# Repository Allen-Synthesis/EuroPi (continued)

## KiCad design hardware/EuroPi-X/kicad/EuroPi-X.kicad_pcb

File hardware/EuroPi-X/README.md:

# EuroPi X

The EuroPi X is an improved hardware version of the EuroPi. Its exact feature set is yet to be decided, but likely additions are more inputs, more outputs, better noise performance for inputs, better accuracy for outputs, a larger display, and larger flash storage.

Suggested features:
- RGB LEDs for outputs
  - [Neopixels](https://www.adafruit.com/product/4492?gclid=Cj0KCQjw2cWgBhDYARIsALggUhp21QpzSRPmMwkA5GLrfMsx_jSPfgyTrgrEi0MlV2bsC2WGbknoDSoaAqggEALw_wcB)?
  - Colour matches output type e.g. red for gate, blue for CV, green for 1v/oct
  - Colour determined automatically in code when a method is used, e.g. cv1.on() would automatically set it to red as a gate type
- DAC outputs (>=12 bit)
  - [MCP4728](https://shop.pimoroni.com/products/adafruit-mcp4728-quad-dac-with-eeprom-stemma-qt-qwiic?variant=31458498412627&currency=GBP&utm_source=google&utm_medium=cpc&utm_campaign=google+shopping?utm_source=google&utm_medium=surfaces&utm_campaign=shopping&gclid=Cj0KCQjwtsCgBhDEARIsAE7RYh3qANxNiQCtKDUFhGal1OTP4WOT_NSxUyUTKL1Pj_3x2VDyPnRayScaAk5DEALw_wcB)? 12 bit, 4 channel
  - Bipolar https://tinyurl.com/2abku7y3, jumper on the back of the module to set the mode, GPIO detects mode to allow code adjustments:

- More inputs
  - 4 inputs can fit in 8HP
- Higher performance CV inputs
  - External ADC, maybe with higher resolution
  - Separate analogue and digital power supplies using RP2040 AGND
- Ability to use +5V rail instead of internally generated
  - 16 pin header
  - Automatically use +5V rail if present, default to internally generated if not
- Make unused GPIO and USB signals accessible from the back
  - Keep one I2C/SPI bus unused so users don't have to worry about address clashes
  - Make sure USB signals are length matched
- Larger display (128x64 or larger)
  - [SSD1306](https://www.buydisplay.com/serial-spi-1-3-inch-128x64-oled-display-module-ssd1306-white-on-black) without breakout board (use Izaak's in progress board?) 
- Bipolar inputs
- Bipolar outputs
- Programmable I/O to allow unipolar or bipolar usage
  - Analogue switch IC? [DG4051 octa analog switch](https://www.mouser.co.uk/ProductDetail/Vishay-Siliconix/DG4051EEQ-T1-GE3?qs=367PjNmvCmmPtnHZ5hoXyA%3D%3D)
- Front access USB
- Front access reset and bootsel
- MicroSD slot for increased storage
- Increased flash by default
- Automatic detection of variant i.e. X or normal hardware
  - One GPIO tied to 3.3V, module detects it's an X if GPIO is high
  - Also set in config settings if module can't detect automatically

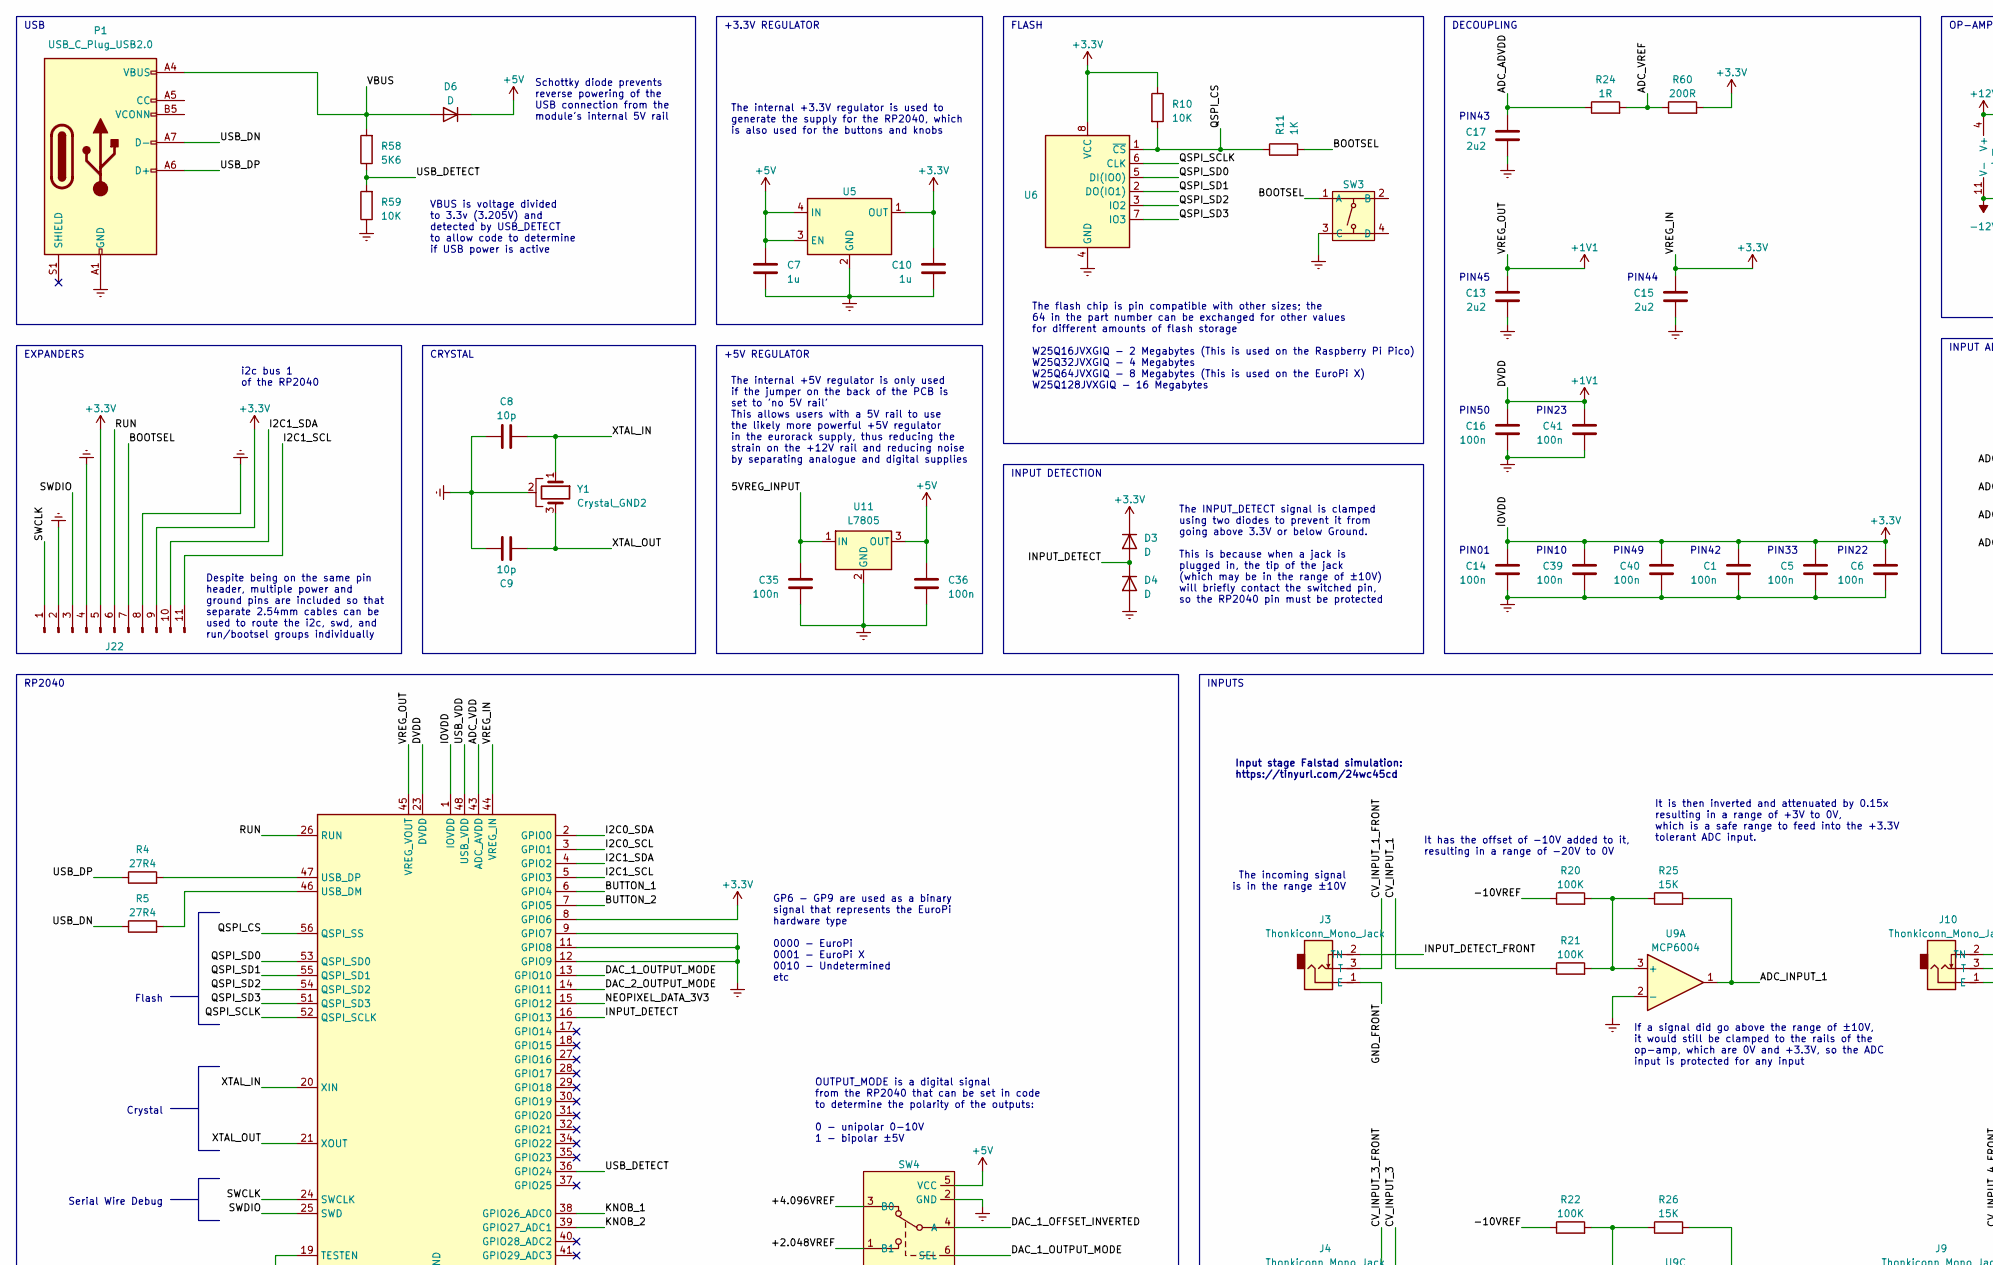
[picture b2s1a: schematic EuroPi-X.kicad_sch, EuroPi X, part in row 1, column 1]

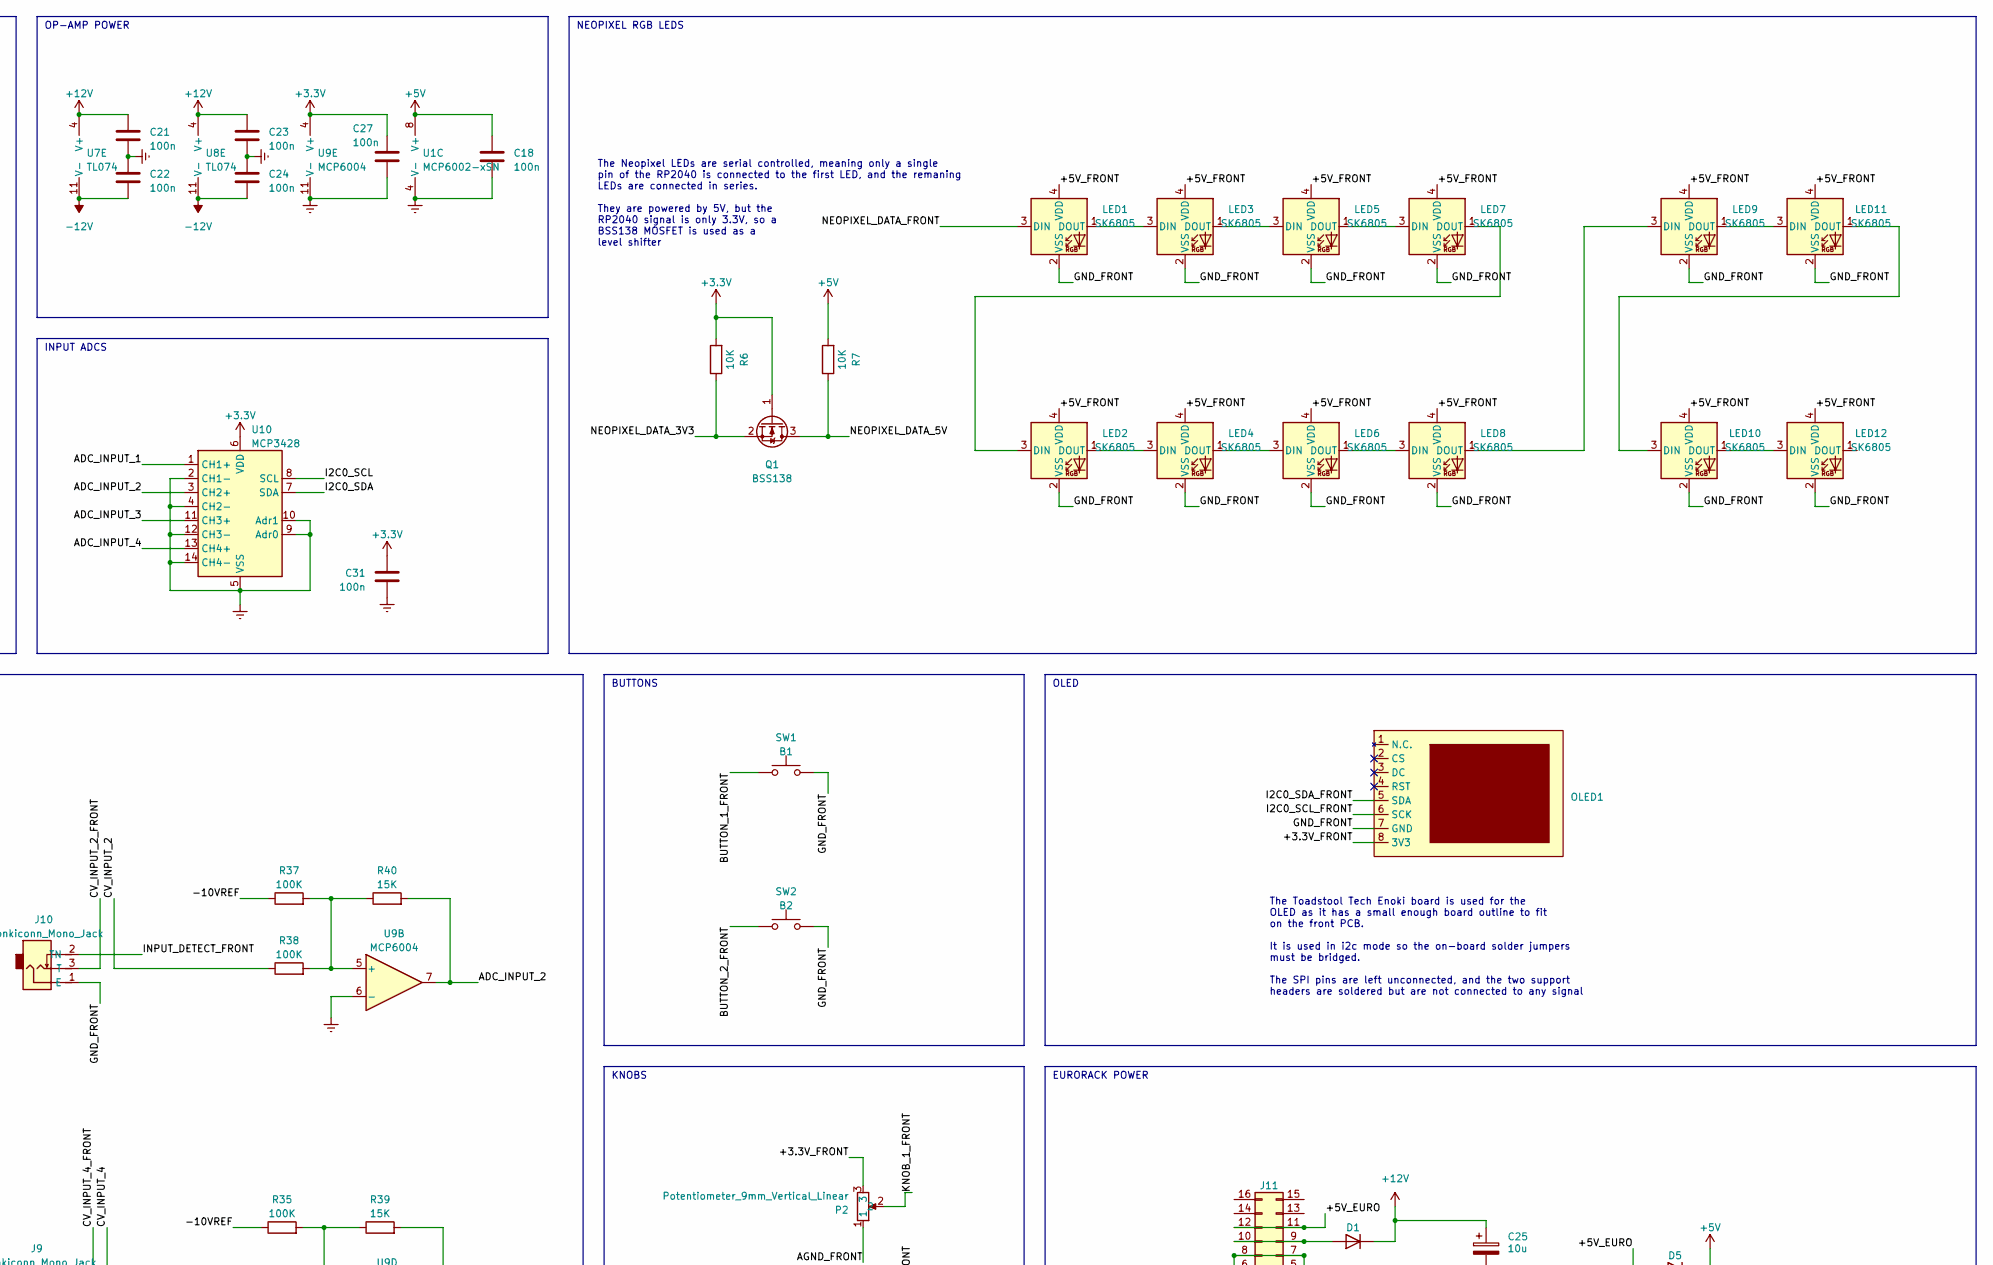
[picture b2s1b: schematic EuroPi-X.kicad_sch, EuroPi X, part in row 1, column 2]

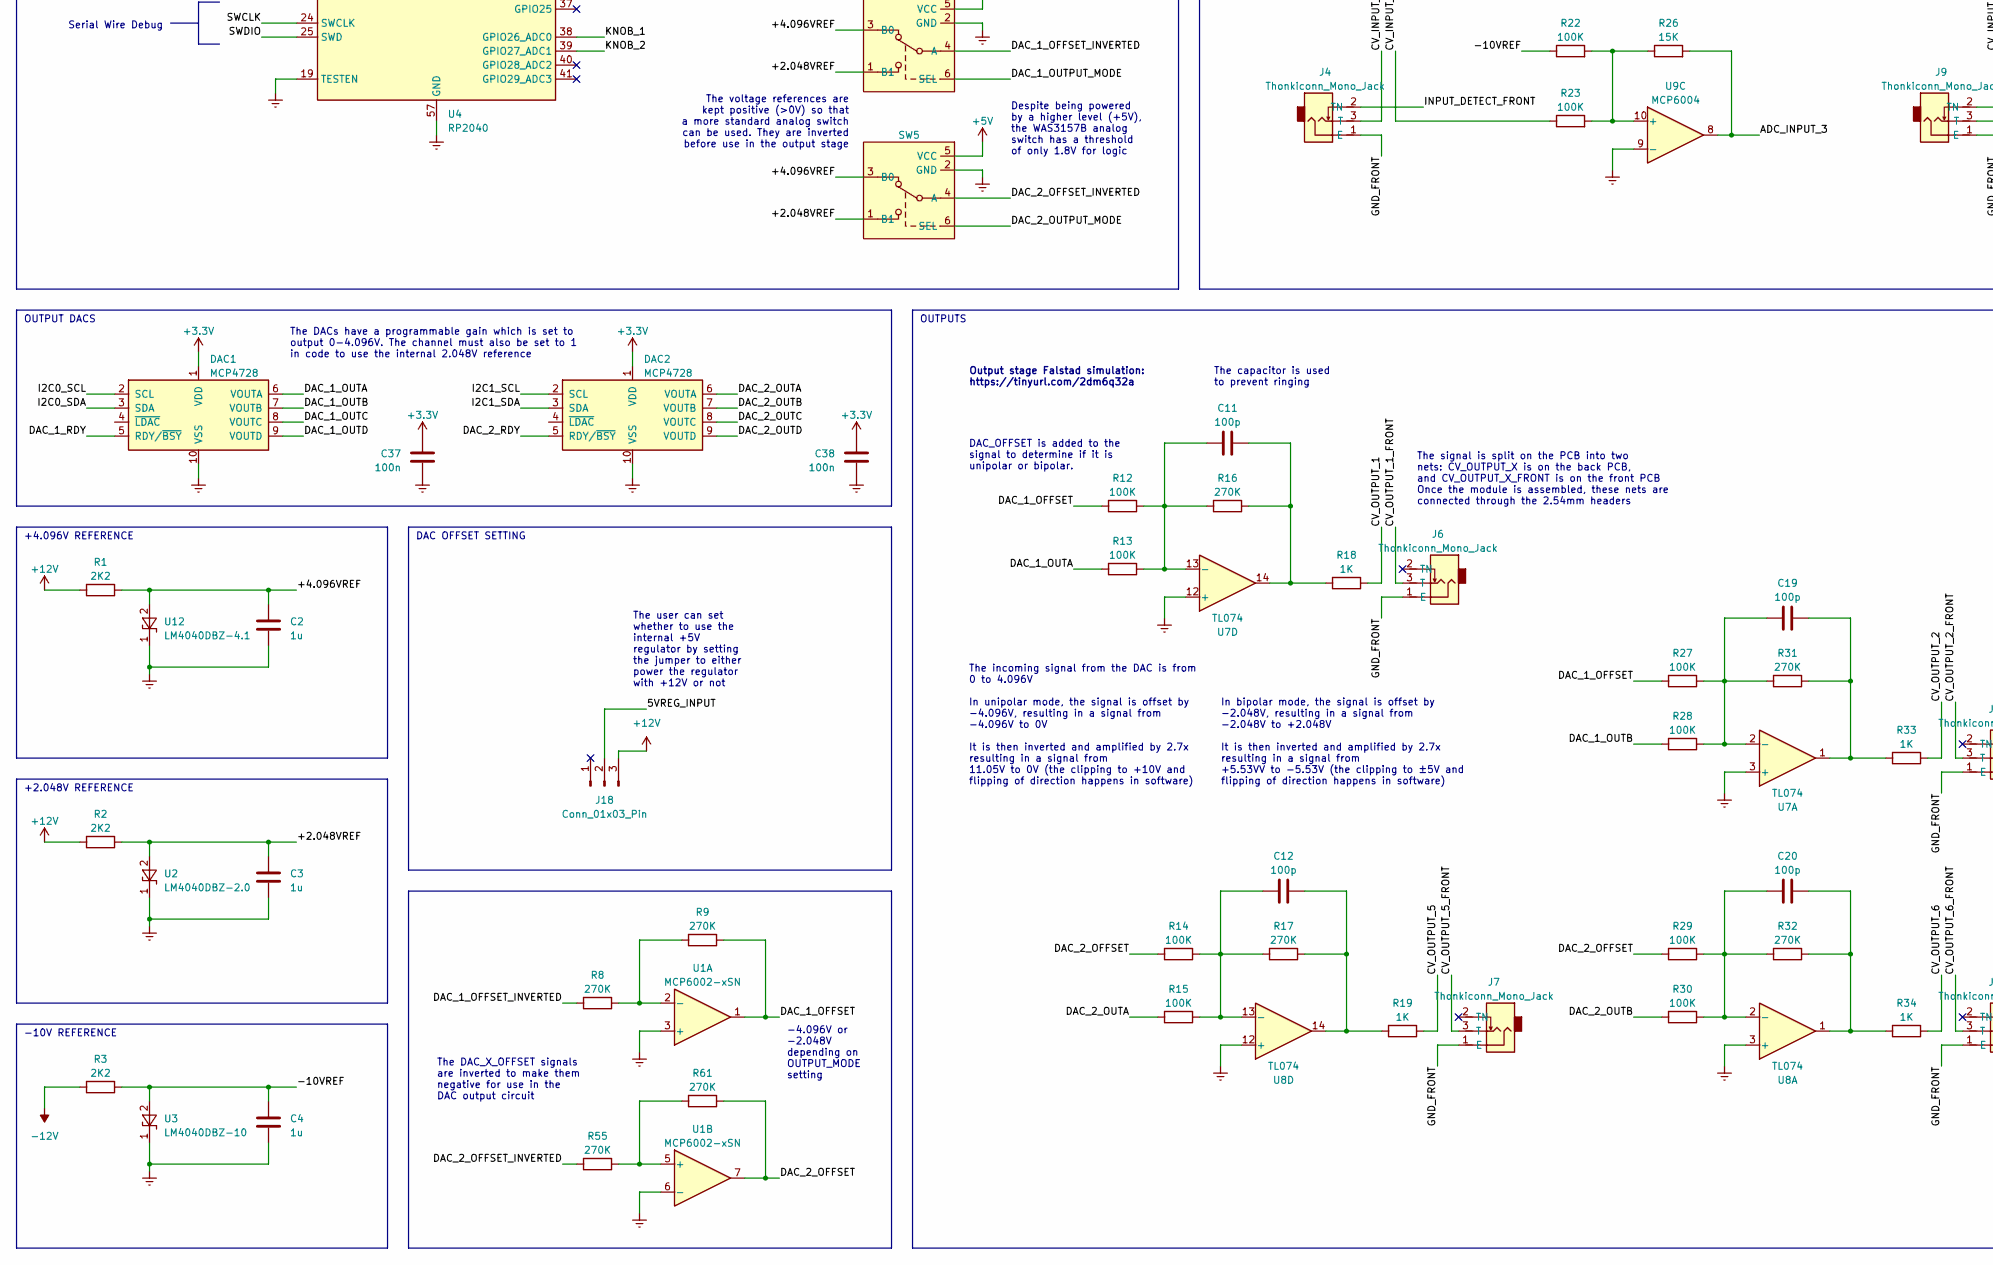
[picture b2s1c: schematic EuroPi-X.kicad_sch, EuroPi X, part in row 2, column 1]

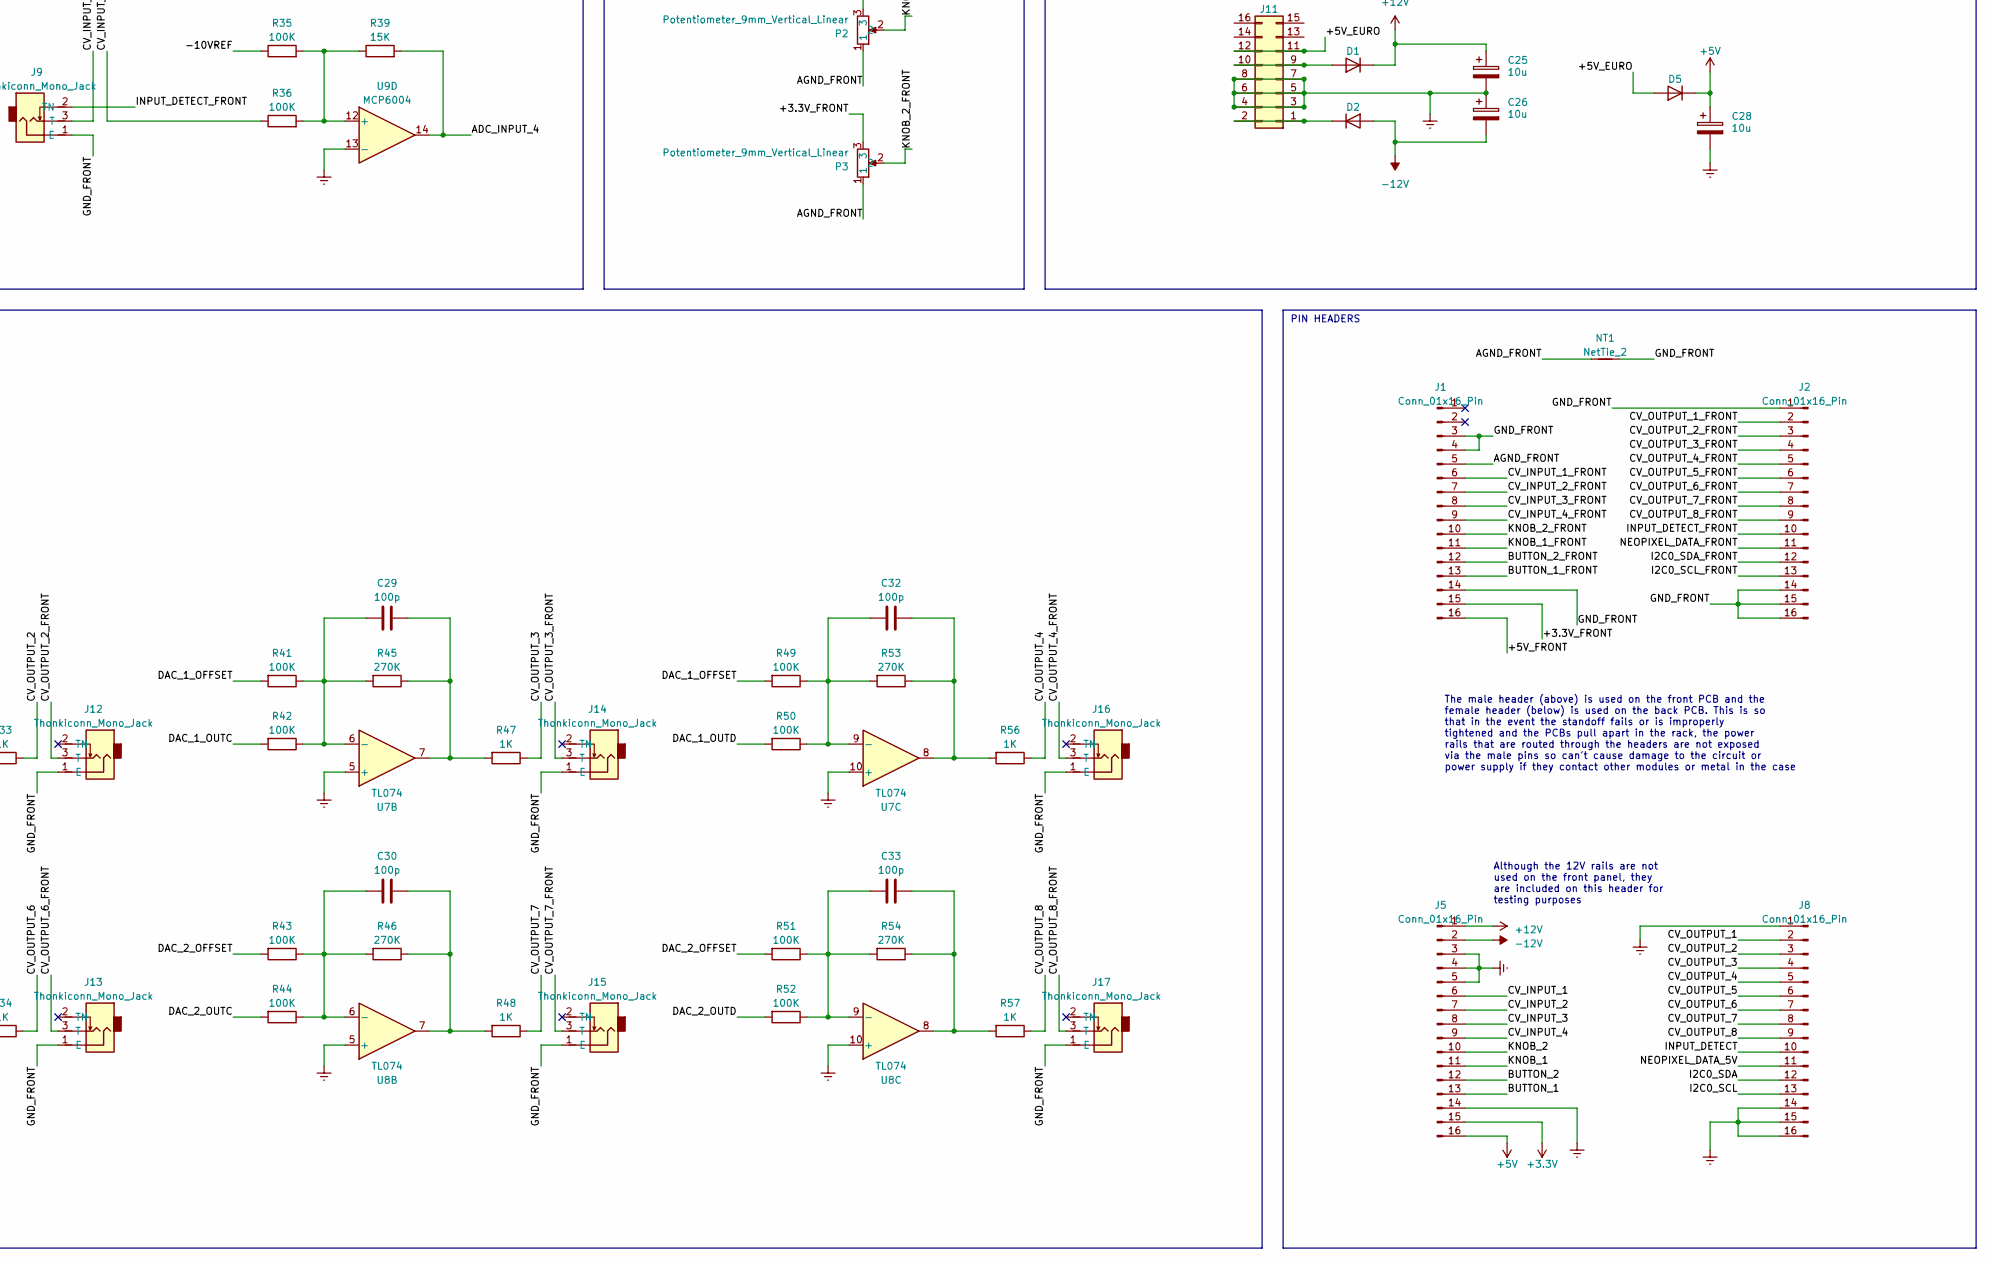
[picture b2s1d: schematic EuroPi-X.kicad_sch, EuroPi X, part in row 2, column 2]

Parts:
C1, C5, C6, C14, C16, C18, C21, C22, C23, C24, C27, C31, C35, C36, C37, C38, C39, C40, C41: 100n; C_0402_1005Metric; JLC C1525
C2, C3, C4, C7, C10: 1u; C_0402_1005Metric; JLC C52923
C8, C9: 10p; C_0402_1005Metric; JLC C32949
C11, C12, C19, C20, C29, C30, C32, C33: 100p; C_0402_1005Metric; JLC C1546
C13, C15, C17: 2u2; C_0402_1005Metric; JLC C12530
C25, C26, C28: 10u; C_0805_2012Metric; JLC C15850
D1, D2, D5: type="D" model="DIODE" lib=""; D_SMA; JLC C95872
D3, D4, D6: D; D_SOD-123; JLC C8598
DAC1, DAC2: MCP4728; MSOP-10_3x3mm_P0.5mm; JLC C478093
J1, J2: Conn_01x16_Pin; PinHeader_1x16_P2.54mm_Vertical
J3, J4, J6, J7, J9, J10, J12, J13, J14, J15, J16, J17: Thonkiconn_Mono_Jack; Thonkiconn Mono Jack
J5, J8: Conn_01x16_Pin; PinSocket_1x16_P2.54mm_Vertical
J11: Conn_02x08_Odd_Even; Eurorack Power Header 16 Pin Unlabeled
J18: Conn_01x03_Pin; PinHeader_1x03_P2.54mm_Vertical
J22: Conn_01x11_Pin; PinHeader_1x11_P2.54mm_Vertical
LED1, LED2, LED3, LED4, LED5, LED6, LED7, LED8, LED9, LED10, LED11, LED12: SK6805; LED_SK6805_PLCC4_2.4x2.7mm_P1.3mm
NT1: NetTie_2; NetTie-2_SMD_Pad0.5mm
OLED1: Enoki OLED SSD1306 128x64
P1: USB_C_Plug_USB2.0; USB_C_Receptacle_G-Switch_GT-USB-7010ASV; JLC C2927037
P2, P3: Potentiometer_9mm_Vertical_Linear; Potentiometer 9mm Vertical Linear Centred
Q1: BSS138; SOT-23; JLC C112239
R1, R2, R3: 2K2; R_0402_1005Metric; JLC C25879
R4, R5: 27R4; R_0402_1005Metric; JLC C25100
R6, R7, R10, R59: 10K; R_0402_1005Metric; JLC C25744
R8, R9, R16, R17, R31, R32, R45, R46, R53, R54, R55, R61: 270K; R_0402_1005Metric; JLC C170277
R11, R18, R19, R33, R34, R47, R48, R56, R57: 1K; R_0402_1005Metric; JLC C11702
R12, R13, R14, R15, R20, R21, R22, R23, R27, R28, R29, R30, R35, R36, R37, R38, R41, R42, R43, R44, R49, R50, R51, R52: 100K; R_0402_1005Metric; JLC C25741
R24: 1R; R_0402_1005Metric; JLC C25086
R25, R26, R39, R40: 15K; R_0402_1005Metric; JLC C25756
R58: 5K6; R_0402_1005Metric; JLC C25092
R60: 200R; R_0402_1005Metric; JLC C25087
SW1: B1; Switch Tactile Momentary C&K
SW2: B2; Switch Tactile Momentary C&K
SW3: TS-1187A-B-A-B; JLC C318884
SW4, SW5: SOT-363_SC-70-6; JLC C213161
U1: MCP6002-xSN; SOIC-8_3.9x4.9mm_P1.27mm; JLC Rotation Offset 270
U2: LM4040DBZ-2.0; SOT-23; JLC C144273
U3: LM4040DBZ-10; SOT-23; JLC C129969
U4: RP2040; QFN-56-1EP_7x7mm_P0.4mm_EP3.2x3.2mm; JLC C2040
U5: SOT-23-3; JLC C5446
U6: SOIC-8_5.23x5.23mm_P1.27mm; JLC C2940195
U7, U8: TL074; SOIC-14_3.9x8.7mm_P1.27mm; JLC C6963
U9: MCP6004; TSSOP-14_4.4x5mm_P0.65mm; JLC C50282
U10: MCP3428; SOIC-14_3.9x8.7mm_P1.27mm; JLC C560166
U11: L7805; TO-252-2; JLC C58069
U12: LM4040DBZ-4.1; SOT-23; JLC C202194
Y1: Crystal_GND2; Crystal_SMD_3225-4Pin_3.2x2.5mm; JLC C9002

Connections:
+1V1: C13.1, C16.1, C41.1, U4.23 (DVDD), U4.45 (VREG_VOUT), U4.50 (DVDD)
+3.3V: C1.1, C5.1, C6.1, C10.1, C14.1, C15.1, C27.1, C31.1, C37.1, C38.1, C39.1, C40.1, D3.1 (K), DAC1.1 (VDD), DAC2.1 (VDD), J5.15, J22.5, J22.9, Q1.1 (G), R6.2, R10.1, R60.2, U4.1 (IOVDD), U4.8 (GPIO6), U4.10 (IOVDD), U4.22 (IOVDD), U4.33 (IOVDD), U4.42 (IOVDD), U4.44 (VREG_IN), U4.49 (IOVDD), U5.1 (OUT), U6.8 (VCC), U9.4 (V+), U10.6 (VDD)
+5V: C7.1, C18.1, C28.1, C36.1, D5.2 (K), D6.1 (K), J5.16, R7.2, SW4.5 (VCC), SW5.5 (VCC), U1.8 (V+), U5.3 (EN), U5.4 (IN), U11.3 (OUT)
+12V: C21.1, C23.1, C25.1, D1.2 (K), J5.1, J18.3, R1.2, R2.2, U7.4 (V+), U8.4 (V+)
-12V: C22.2, C24.2, C26.2, D2.1 (A), J5.2, R3.2, U7.11 (V-), U8.11 (V-)
/5VREG_INPUT: C35.1, J18.2, U11.1 (IN)
/+2.048VREF: C3.1, R2.1, SW4.1 (B1), SW5.1 (B1), U2.2 (A)
/+3.3V_FRONT: J1.15, OLED1.8 (3V3), P2.3, P3.3
/+4.096VREF: C2.1, R1.1, SW4.3 (B0), SW5.3 (B0), U12.2 (A)
/+5V_EURO: D5.1 (A), J11.11, J11.12
/+5V_FRONT: J1.16, LED1.4 (VDD), LED2.4 (VDD), LED3.4 (VDD), LED4.4 (VDD), LED5.4 (VDD), LED6.4 (VDD), LED7.4 (VDD), LED8.4 (VDD), LED9.4 (VDD), LED10.4 (VDD), LED11.4 (VDD), LED12.4 (VDD)
/-10VREF: C4.1, R3.1, R20.1, R22.1, R35.1, R37.1, U3.2 (A)
/ADC_ADVDD: C17.1, R24.1
/ADC_INPUT_1: R25.2, U9.1, U10.1 (CH1+)
/ADC_INPUT_2: R40.2, U9.7, U10.3 (CH2+)
/ADC_INPUT_3: R26.2, U9.8, U10.11 (CH3+)
/ADC_INPUT_4: R39.2, U9.14, U10.13 (CH4+)
/ADC_VDD: U4.43 (ADC_AVDD)
/ADC_VREF: R24.2, R60.1
/AGND_FRONT: J1.5, NT1.1, P2.1, P3.1
/BOOTSEL: J22.7, R11.2, SW3.1 (A)
/BUTTON_1: J5.13, U4.6 (GPIO4)
/BUTTON_1_FRONT: J1.13, SW1.1
/BUTTON_2: J5.12, U4.7 (GPIO5)
/BUTTON_2_FRONT: J1.12, SW2.1
/CV_INPUT_1: J5.6, R21.1
/CV_INPUT_1_FRONT: J1.6, J3.3 (T)
/CV_INPUT_2: J5.7, R38.1
/CV_INPUT_2_FRONT: J1.7, J10.3 (T)
/CV_INPUT_3: J5.8, R23.1
/CV_INPUT_3_FRONT: J1.8, J4.3 (T)
/CV_INPUT_4: J5.9, R36.1
/CV_INPUT_4_FRONT: J1.9, J9.3 (T)
/CV_OUTPUT_1: J8.2, R18.1
/CV_OUTPUT_1_FRONT: J2.2, J6.3 (T)
/CV_OUTPUT_2: J8.3, R33.1
/CV_OUTPUT_2_FRONT: J2.3, J12.3 (T)
/CV_OUTPUT_3: J8.4, R47.1
/CV_OUTPUT_3_FRONT: J2.4, J14.3 (T)
/CV_OUTPUT_4: J8.5, R56.1
/CV_OUTPUT_4_FRONT: J2.5, J16.3 (T)
/CV_OUTPUT_5: J8.6, R19.1
/CV_OUTPUT_5_FRONT: J2.6, J7.3 (T)
/CV_OUTPUT_6: J8.7, R34.1
/CV_OUTPUT_6_FRONT: J2.7, J13.3 (T)
/CV_OUTPUT_7: J8.8, R48.1
/CV_OUTPUT_7_FRONT: J2.8, J15.3 (T)
/CV_OUTPUT_8: J8.9, R57.1
/CV_OUTPUT_8_FRONT: J2.9, J17.3 (T)
/DAC_1_OFFSET: R9.1, R12.2, R27.2, R41.2, R49.2, U1.1
/DAC_1_OFFSET_INVERTED: R8.2, SW4.4 (A)
/DAC_1_OUTA: DAC1.6 (VOUTA), R13.2
/DAC_1_OUTB: DAC1.7 (VOUTB), R28.2
/DAC_1_OUTC: DAC1.8 (VOUTC), R42.2
/DAC_1_OUTD: DAC1.9 (VOUTD), R50.2
/DAC_1_OUTPUT_MODE: SW4.6 (SEL), U4.13 (GPIO10)
/DAC_1_RDY: DAC1.5 (RDY/~BSY)
/DAC_2_OFFSET: R14.2, R29.2, R43.2, R51.2, R61.1, U1.7
/DAC_2_OFFSET_INVERTED: R55.2, SW5.4 (A)
/DAC_2_OUTA: DAC2.6 (VOUTA), R15.2
/DAC_2_OUTB: DAC2.7 (VOUTB), R30.2
/DAC_2_OUTC: DAC2.8 (VOUTC), R44.2
/DAC_2_OUTD: DAC2.9 (VOUTD), R52.2
/DAC_2_OUTPUT_MODE: SW5.6 (SEL), U4.14 (GPIO11)
/DAC_2_RDY: DAC2.5 (RDY/~BSY)
/GND_FRONT: J1.3, J1.4, J1.14, J2.1, J2.14, J2.15, J2.16, J3.1 (E), J4.1 (E), J6.1 (E), J7.1 (E), J9.1 (E), J10.1 (E), J12.1 (E), J13.1 (E), J14.1 (E), J15.1 (E), J16.1 (E), J17.1 (E), LED1.2 (VSS), LED2.2 (VSS), LED3.2 (VSS), LED4.2 (VSS), LED5.2 (VSS), LED6.2 (VSS), LED7.2 (VSS), LED8.2 (VSS), LED9.2 (VSS), LED10.2 (VSS), LED11.2 (VSS), LED12.2 (VSS), NT1.2, OLED1.7 (GND), SW1.2, SW2.2
/I2C0_SCL: DAC1.2 (SCL), J8.13, U4.3 (GPIO1), U10.8 (SCL)
/I2C0_SCL_FRONT: J2.13, OLED1.6 (SCK)
/I2C0_SDA: DAC1.3 (SDA), J8.12, U4.2 (GPIO0), U10.7 (SDA)
/I2C0_SDA_FRONT: J2.12, OLED1.5 (SDA)
/I2C1_SCL: DAC2.2 (SCL), J22.11, U4.5 (GPIO3)
/I2C1_SDA: DAC2.3 (SDA), J22.10, U4.4 (GPIO2)
/INPUT_DETECT: D3.2 (A), D4.1 (K), J8.10, U4.16 (GPIO13)
/INPUT_DETECT_FRONT: J2.10, J3.2 (TN), J4.2 (TN), J9.2 (TN), J10.2 (TN)
/KNOB_1: J5.11, U4.38 (GPIO26_ADC0)
/KNOB_1_FRONT: J1.11, P2.2
/KNOB_2: J5.10, U4.39 (GPIO27_ADC1)
/KNOB_2_FRONT: J1.10, P3.2
/NEOPIXEL_DATA_3V3: Q1.2 (S), R6.1, U4.15 (GPIO12)
/NEOPIXEL_DATA_5V: J8.11, Q1.3 (D), R7.1
/NEOPIXEL_DATA_FRONT: J2.11, LED1.3 (DIN)
/QSPI_CS: R10.2, R11.1, U4.56 (QSPI_SS), U6.1 (~CS)
/QSPI_SCLK: U4.52 (QSPI_SCLK), U6.6 (CLK)
/QSPI_SD0: U4.53 (QSPI_SD0), U6.5 (DI(IO0))
/QSPI_SD1: U4.55 (QSPI_SD1), U6.2 (DO(IO1))
/QSPI_SD2: U4.54 (QSPI_SD2), U6.3 (IO2)
/QSPI_SD3: U4.51 (QSPI_SD3), U6.7 (IO3)
/RUN: J22.6, U4.26 (RUN)
/SWCLK: J22.1, U4.24 (SWCLK)
/SWDIO: J22.3, U4.25 (SWD)
/USB_DETECT: R58.1, R59.2, U4.36 (GPIO24)
/USB_DN: P1.A7 (D-), R5.1
/USB_DP: P1.A6 (D+), R4.1
/USB_VDD: U4.48 (USB_VDD)
/VBUS: D6.2 (A), P1.A4 (VBUS), P1.A9 (VBUS), P1.B4 (VBUS), P1.B9 (VBUS), R58.2
/XTAL_IN: C8.2, U4.20 (XIN), Y1.1
/XTAL_OUT: C9.2, U4.21 (XOUT), Y1.3
Earth: C1.2, C2.2, C3.2, C4.2, C5.2, C6.2, C7.2, C8.1, C9.1, C10.2, C13.2, C14.2, C15.2, C16.2, C17.2, C18.2, C21.2, C22.1, C23.2, C24.1, C25.2, C26.1, C27.2, C28.2, C31.2, C35.2, C36.2, C37.2, C38.2, C39.2, C40.2, C41.2, D4.2 (A), DAC1.10 (VSS), DAC2.10 (VSS), J5.3, J5.4, J5.5, J5.14, J8.1, J8.14, J8.15, J8.16, J11.3, J11.4, J11.5, J11.6, J11.7, J11.8, J22.2, J22.4, J22.8, P1.A1 (GND), P1.A12 (GND), P1.B1 (GND), P1.B12 (GND), R59.1, SW3.3 (C), SW4.2 (GND), SW5.2 (GND), U1.3 (+), U1.4 (V-), U1.6 (-), U2.1 (K), U3.1 (K), U4.9 (GPIO7), U4.11 (GPIO8), U4.12 (GPIO9), U4.19 (TESTEN), U4.57 (GND), U5.2 (GND), U5.5 (GND), U6.4 (GND), U7.3 (+), U7.5 (+), U7.10 (+), U7.12 (+), U8.3 (+), U8.5 (+), U8.10 (+), U8.12 (+), U9.2 (-), U9.6 (-), U9.9 (-), U9.11 (V-), U9.13 (-), U10.2 (CH1-), U10.4 (CH2-), U10.5 (VSS), U10.9 (Adr0), U10.10 (Adr1), U10.12 (CH3-), U10.14 (CH4-), U11.2 (GND), U12.1 (K), Y1.2
unnamed: C11.2, R16.1, R18.2, U7.14
unnamed: C12.2, R17.1, R19.2, U8.14
unnamed: C19.2, R31.1, R33.2, U7.1
unnamed: C20.2, R32.1, R34.2, U8.1
unnamed: C29.2, R45.1, R47.2, U7.7
unnamed: C30.2, R46.1, R48.2, U8.7
unnamed: C32.2, R53.1, R56.2, U7.8
unnamed: C33.2, R54.1, R57.2, U8.8
unnamed: D1.1 (A), J11.9, J11.10
unnamed: D2.2 (K), J11.1, J11.2
unnamed: LED1.1 (DOUT), LED3.3 (DIN)
unnamed: LED2.3 (DIN), LED7.1 (DOUT)
unnamed: LED2.1 (DOUT), LED4.3 (DIN)
unnamed: LED3.1 (DOUT), LED5.3 (DIN)
unnamed: LED4.1 (DOUT), LED6.3 (DIN)
unnamed: LED5.1 (DOUT), LED7.3 (DIN)
unnamed: LED6.1 (DOUT), LED8.3 (DIN)
unnamed: LED8.1 (DOUT), LED9.3 (DIN)
unnamed: LED10.3 (DIN), LED11.1 (DOUT)
unnamed: LED10.1 (DOUT), LED12.3 (DIN)
unnamed: LED9.1 (DOUT), LED11.3 (DIN)
unnamed: R8.1, R9.2, U1.2 (-)
unnamed: R55.1, R61.2, U1.5 (+)
unnamed: R5.2, U4.46 (USB_DM)
unnamed: R4.2, U4.47 (USB_DP)
unnamed: C19.1, R27.1, R28.1, R31.2, U7.2 (-)
unnamed: C29.1, R41.1, R42.1, R45.2, U7.6 (-)
unnamed: C32.1, R49.1, R50.1, R53.2, U7.9 (-)
unnamed: C11.1, R12.1, R13.1, R16.2, U7.13 (-)
unnamed: C20.1, R29.1, R30.1, R32.2, U8.2 (-)
unnamed: C30.1, R43.1, R44.1, R46.2, U8.6 (-)
unnamed: C33.1, R51.1, R52.1, R54.2, U8.9 (-)
unnamed: C12.1, R14.1, R15.1, R17.2, U8.13 (-)
unnamed: R20.2, R21.2, R25.1, U9.3 (+)
unnamed: R37.2, R38.2, R40.1, U9.5 (+)
unnamed: R22.2, R23.2, R26.1, U9.10 (+)
unnamed: R35.2, R36.2, R39.1, U9.12 (+)

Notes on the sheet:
OP-AMP POWER
+5V REGULATOR
DAC OFFSET SETTING
DAC_OFFSET is added to the signal to determine if it is unipolar or bipolar.
Crystal
The INPUT_DETECT signal is clamped using two diodes to prevent it from going above 3.3V or below Ground. This is because when a jack is plugged in, the tip of the jack (which may be in the range of ±10V) will briefly contact the switched pin, so the RP2040 pin must be protected
The DAC_X_OFFSET signals are inverted to make them negative for use in the DAC output circuit
OUTPUT_MODE is a digital signal from the RP2040 that can be set in code to determine the polarity of the outputs: 0 - unipolar 0-10V 1 - bipolar ±5V
PIN45
PIN44
+3.3V REGULATOR
The internal +3.3V regulator is used to generate the supply for the RP2040, which is also used for the buttons and knobs
In bipolar mode, the signal is offset by -2.048V, resulting in a signal from -2.048V to +2.048V It is then inverted and amplified by 2.7x resulting in a signal from +5.53VV to -5.53V (the clipping to ±5V and flipping of direction happens in software)
USB
PIN50
GP6 - GP9 are used as a binary signal that represents the EuroPi hardware type 0000 - EuroPi 0001 - EuroPi X 0010 - Undetermined etc
INPUT ADCS
The signal is split on the PCB into two nets: CV_OUTPUT_X is on the back PCB, and CV_OUTPUT_X_FRONT is on the front PCB Once the module is assembled, these nets are connected through the 2.54mm headers
The male header (above) is used on the front PCB and the female header (below) is used on the back PCB. This is so that in the event the standoff fails or is improperly tightened and the PCBs pull apart in the rack, the power rails that are routed through the headers are not exposed via the male pi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
+2.048V REFERENCE
RP2040
The user can set whether to use the internal +5V regulator by setting the jumper to either power the regulator with +12V or not
INPUTS
The internal +5V regulator is only used if the jumper on the back of the PCB is set to 'no 5V rail' This allows users with a 5V rail to use the likely more powerful +5V regulator in the eurorack supply, thus reducing the strain on the +12V rail and reducing noise by separating analogue and digital 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
PIN22
PIN49
The incoming signal from the DAC is from 0 to 4.096V In unipolar mode, the signal is offset by -4.096V, resulting in a signal from -4.096V to 0V It is then inverted and amplified by 2.7x resulting in a signal from 11.05V to 0V (the clipping to +10V and flipping of direction happens in software)
INPUT DETECTION
If a signal did go above the range of ±10V, it would still be clamped to the rails of the op-amp, which are 0V and +3.3V, so the ADC input is protected for any input
It has the offset of -10V added to it, resulting in a range of -20V to 0V
FLASH
PIN43
PIN42
PIN33
DECOUPLING
KNOBS
Flash
OUTPUT DACS
The capacitor is used to prevent ringing
-10V REFERENCE

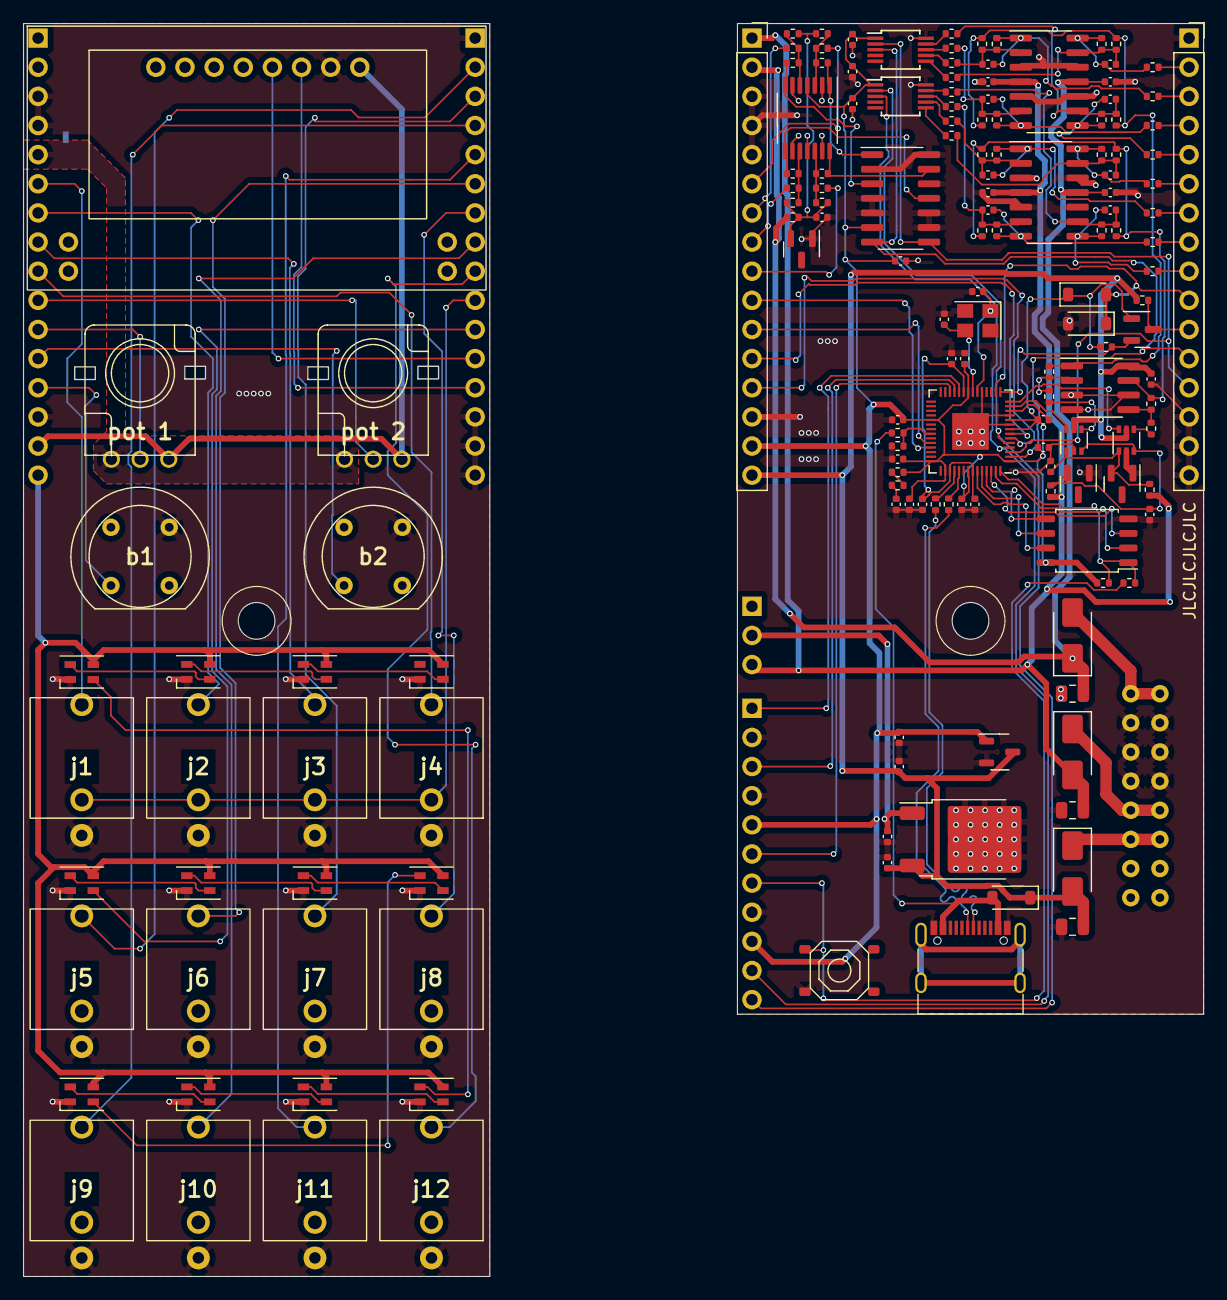
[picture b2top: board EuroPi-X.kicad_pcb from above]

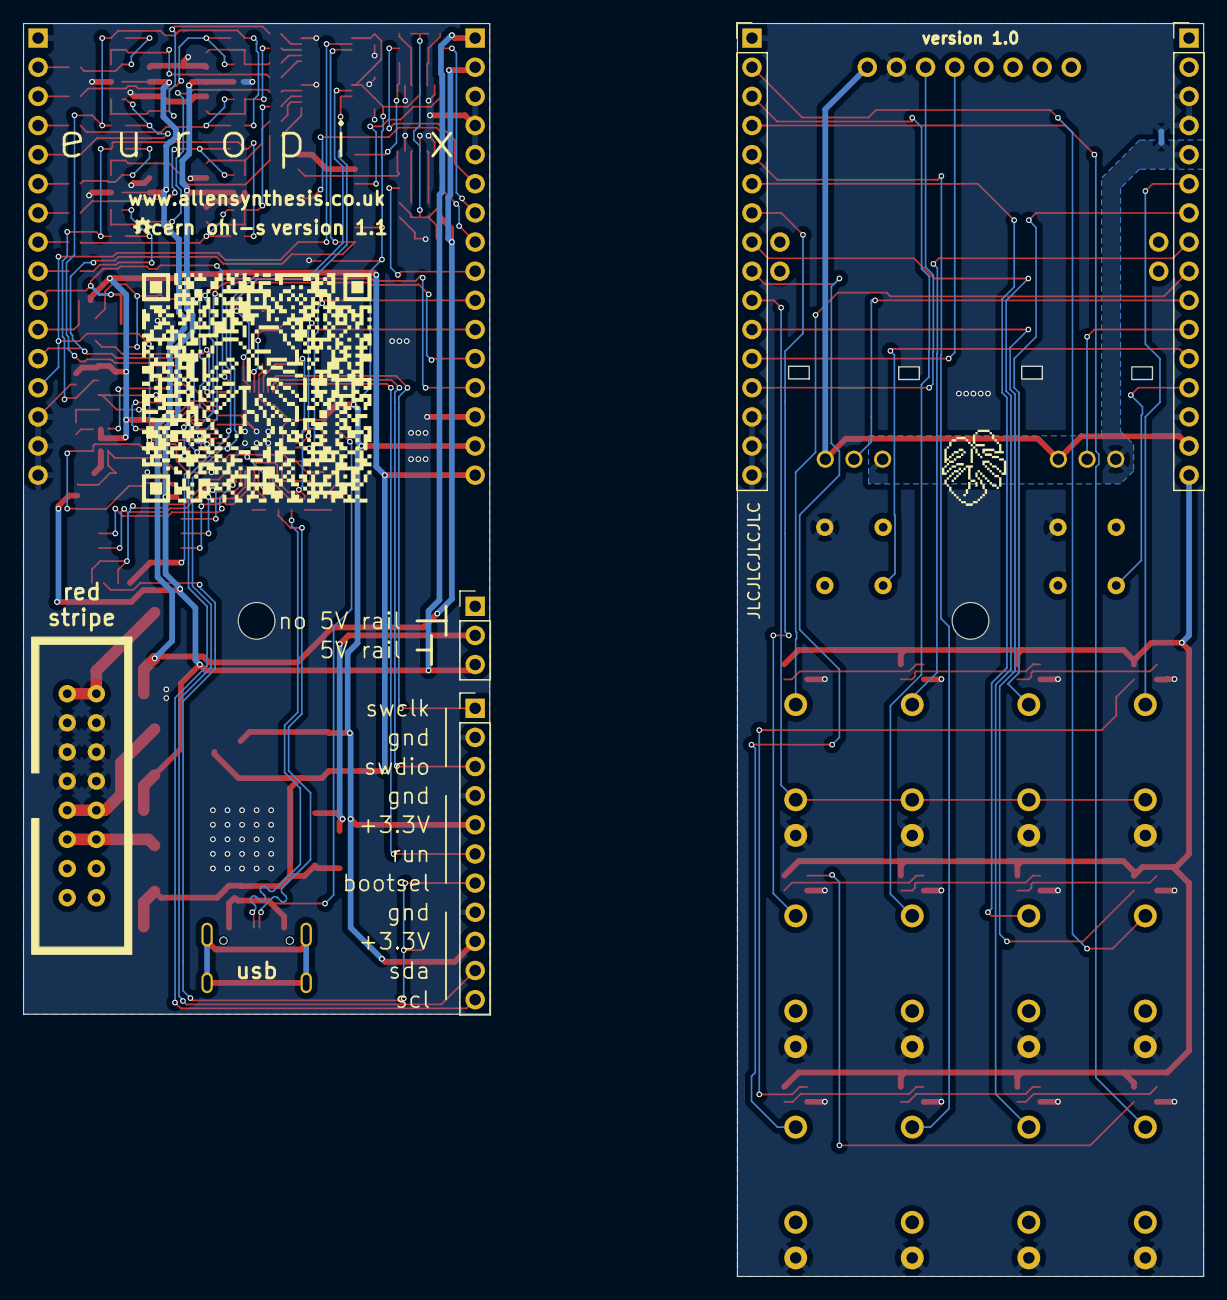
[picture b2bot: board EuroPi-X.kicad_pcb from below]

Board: 2 copper layers, 40.6 x 86.4 mm, 164 parts (6 on the bottom side), 131 nets.

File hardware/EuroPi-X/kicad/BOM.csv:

Designator,Footprint,Quantity,Value,LCSC Part #
"C1, C14, C16, C21, C22, C23, C24, C27, C31, C35, C36, C37, C38, C39, C40, C41, C5, C6",402,18,100n,C1525
"C10, C2, C3, C4, C7",402,5,1u,C52923
"C11, C12, C19, C20, C29, C30, C32, C33",402,8,100p,C1546
"C13, C15, C17",402,3,2u2,C12530
"C25, C26, C28",805,3,10u,C15850
"C8, C9",402,2,10p,C32949
"D1, D2, D5",D_SMA,3,"type=""D"" model=""DIODE"" lib=""""",C95872
"D3, D4, D6",D_SOD-123,3,D,C8598
"DAC1, DAC2",MSOP-10_3x3mm_P0.5mm,2,MCP4728,C478093
P1,USB_C_Receptacle_G-Switch_GT-USB-7010ASV,1,USB_C_Plug_USB2.0,C2927037
Q1,SOT-23,1,BSS138,C112239
"R1, R2, R3",402,3,2K2,C25879
"R10, R59, R6, R7, R8, R9",402,6,10K,C25744
"R11, R18, R19, R33, R34, R47, R48, R56, R57",402,9,1K,C11702
"R12, R13, R14, R15, R20, R21, R22, R23, R27, R28, R29, R30, R35, R36, R37, R38, R41, R42, R43, R44, R49, R50, R51, R52",402,24,100K,C25741
"R16, R17, R31, R32, R45, R46, R53, R54",402,8,270K,C170277
R24,402,1,1R,C25086
"R25, R26, R39, R40",402,4,15K,C25756
"R4, R5",402,2,27R4,C25100
R58,402,1,5K6,C25908
R60,402,1,200R,C25087
SW3,TS-1187A-B-A-B,1,~,C318884
U10,SOIC-14_3.9x8.7mm_P1.27mm,1,MCP3428,C560166
U11,TO-252-3_TabPin2,1,L7805,C58069
U12,SOT-23,1,LM4040DBZ-4.1,C202194
U2,SOT-23,1,LM4040DBZ-2.0,C144273
U3,SOT-23,1,LM4040DBZ-10,C129969
U4,QFN-56-1EP_7x7mm_P0.4mm_EP3.2x3.2mm,1,RP2040,C2040
U5,SOT-23-3,1,~,C5446
U6,SOIC-8_5.23x5.23mm_P1.27mm,1,~,C2940195
"U7, U8",SOIC-14_3.9x8.7mm_P1.27mm,2,TL074,C6963
U9,TSSOP-14_4.4x5mm_P0.65mm,1,MCP6004,C50282
Y1,Crystal_SMD_3225-4Pin_3.2x2.5mm,1,Crystal_GND2,C9002
